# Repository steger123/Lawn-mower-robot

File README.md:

# Lawn-mower-robot

## The main purpose of the project:

**Create a general, affordable, computational platform, which can be used for small & medium size robots.**

The navivation can be: fully maunal, semi and full autonomouse.
The mechanical side not restricted.
As the project progressing and evolving **You can learn more and more**, **and of course, have the designs and codes for free.**

## Software:

### BASE:
Mission Planner: C#
https://github.com/steger123/Lawn-mower-robot/tree/master/03_Software%20codes/02_C%23_Mission%20planner

### ROVER:
Main MCU : C++ (Arduino)
https://github.com/steger123/Lawn-mower-robot/tree/master/03_Software%20codes/01_C%2B%2B_Arduino/01_Rover/Test_Motor_v12

AI: Python (Jetson NANO)
https://github.com/steger123/Lawn-mower-robot/tree/master/03_Software%20codes/03_Python_AI_Jetson%20Nano/01_myOpenCV

### ROVER Electronic boards:
1. Arduino MEGA later Shieldbuddy TC375 (It has 3 cores !)
2. Custom made shield, sitting on the Arduino MEGA to have enough space for connectors (4xseial, 4xSPI, 3xI2C, buttons, 3xultrasonic sensos, volt & ampere meter etc.).
3. GPS: 2 x GNSS modules with RTK / Xbee. More here: https://github.com/steger123/Lawn-mower-robot/issues/8
5. Base's RTK: simpleRTK2Blite from Ardusimple or GPS Development Tools SparkFun GPS-RTK-SMA Breakout - ZED-F9P
6. Rovers RTK: RTK+INS simpleRTK2B-F9R V3 from Ardusimple or SparkFun Accessories SparkFun GPS-RTK Dead Reckoning Breakout - ZED-F9R
7. Motor controllers: 2x DC
8. RF radio: for additional Base to Rover and back communication (remote controll, getting sensor date from rover to mission control software).
9. Jetson Nano with normal webcam. Communicating via serial port to the MEGA (detect plant diseases, following plant line)
10. Sensors on the shield (utlrasonoic distance, battery volt, curret mesuring, rain etc.)

## Body:
As you like. In scouting for example: 1m x 1m x 0.5m

## Wheels:
As you like. In scouting for example: driven 280 mm in diamteter + castor wheels.
it can be smoot like a bicycle or thick lugs like on a tractor tire (good grippong during scouting on the field).

## Engine/motor:
As you like. In scouting for example: 2x 50W DC motors with encoders. 50 rpm

## Transmission:
As you like. In scouting for example: plannetary gerabox.

## Collaboration (software, electronic hardware, new PCB/shield, mechanical parts etc.):
If You like to join, please contact me:
andras.steger@protonmail.com

More information:
https://github.com/steger123/Lawn-mower-robot/wiki

## Latest news:
https://twitter.com/StegerAndras

Custom robot rover shield for Arduino MEGA or ShieldBuddy TC375:

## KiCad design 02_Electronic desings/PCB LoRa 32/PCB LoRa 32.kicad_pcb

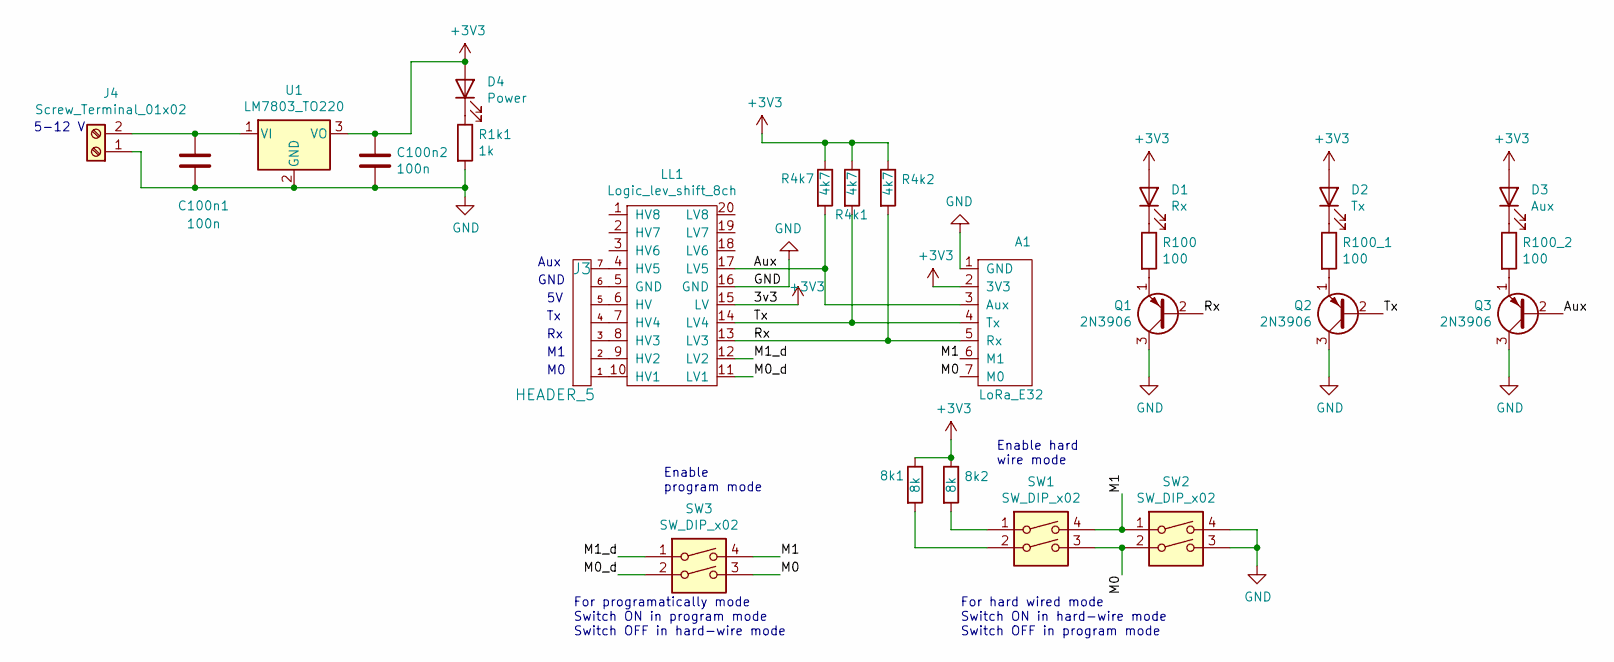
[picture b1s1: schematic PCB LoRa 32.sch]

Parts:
8k1, 8k2: 8k; R_Axial_DIN0204_L3.6mm_D1.6mm_P2.54mm_Vertical
A1: LoRa_E32
C100n1, C100n2: 100n; CP_Radial_Tantal_D5.0mm_P5.00mm
D1: Rx; LED_D5.0mm
D2: Tx; LED_D5.0mm
D3: Aux; LED_D5.0mm
D4: Power; LED_D5.0mm
J3: HEADER_5; JST_XH_B7B-XH-A_1x07_P2.50mm_Vertical
J4: Screw_Terminal_01x02; TerminalBlock_Phoenix_MKDS-1,5-2-5.08_1x02_P5.08mm_Horizont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
LL1: Logic_lev_shift_8ch
Q1, Q2, Q3: 2N3906; TO-92_Inline
R1k1: 1k; R_Axial_DIN0204_L3.6mm_D1.6mm_P2.54mm_Vertical
R4k1, R4k2, R4k7: 4k7; R_Axial_DIN0204_L3.6mm_D1.6mm_P5.08mm_Vertical
R100, R100_1, R100_2: 100; R_Axial_DIN0204_L3.6mm_D1.6mm_P2.54mm_Vertical
SW1, SW2, SW3: SW_DIP_x02; SW_DIP_SPSTx02_Slide_9.78x7.26mm_W7.62mm_P2.54mm
U1: LM7803_TO220; TO-220-3_Vertical

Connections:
+3V3: 8k1.1, 8k2.1, A1.2 (3V3), C100n2.1, D1.2 (A), D2.2 (A), D3.2 (A), D4.2 (A), LL1.15 (LV), R4k1.1, R4k2.1, R4k7.1, U1.3 (VO)
/Aux: A1.3 (Aux), LL1.17 (LV5), Q3.2 (B), R4k7.2
/M0: A1.7 (M0), SW1.3, SW2.2, SW3.3
/M0_d: LL1.11 (LV1), SW3.2
/M1: A1.6 (M1), SW1.4, SW2.1, SW3.4
/M1_d: LL1.12 (LV2), SW3.1
/Rx: A1.5 (Rx), LL1.13 (LV3), Q1.2 (B), R4k2.2
/Tx: A1.4 (Tx), LL1.14 (LV4), Q2.2 (B), R4k1.2
GND: A1.1 (GND), C100n1.2, C100n2.2, J4.1, LL1.16 (GND), Q1.3 (C), Q2.3 (C), Q3.3 (C), R1k1.2, SW2.3, SW2.4, U1.2 (GND)
unnamed: 8k1.2, SW1.2
unnamed: 8k2.2, SW1.1
unnamed: C100n1.1, J4.2, U1.1 (VI)
unnamed: D1.1 (K), R100.1
unnamed: D2.1 (K), R100_1.1
unnamed: D3.1 (K), R100_2.1
unnamed: D4.1 (K), R1k1.1
unnamed: J3.1, LL1.10 (HV1)
unnamed: J3.2, LL1.9 (HV2)
unnamed: J3.3, LL1.8 (HV3)
unnamed: J3.4, LL1.7 (HV4)
unnamed: J3.5, LL1.6 (HV)
unnamed: J3.6, LL1.5 (GND)
unnamed: J3.7, LL1.4 (HV5)
unnamed: Q1.1 (E), R100.2
unnamed: Q2.1 (E), R100_1.2
unnamed: Q3.1 (E), R100_2.2

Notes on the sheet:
5-12 V
For programatically mode Switch ON in program mode Switch OFF in hard-wire mode
For hard wired mode Switch ON in hard-wire mode Switch OFF in program mode
GND
Aux
Enable hard wire mode
Enable program mode

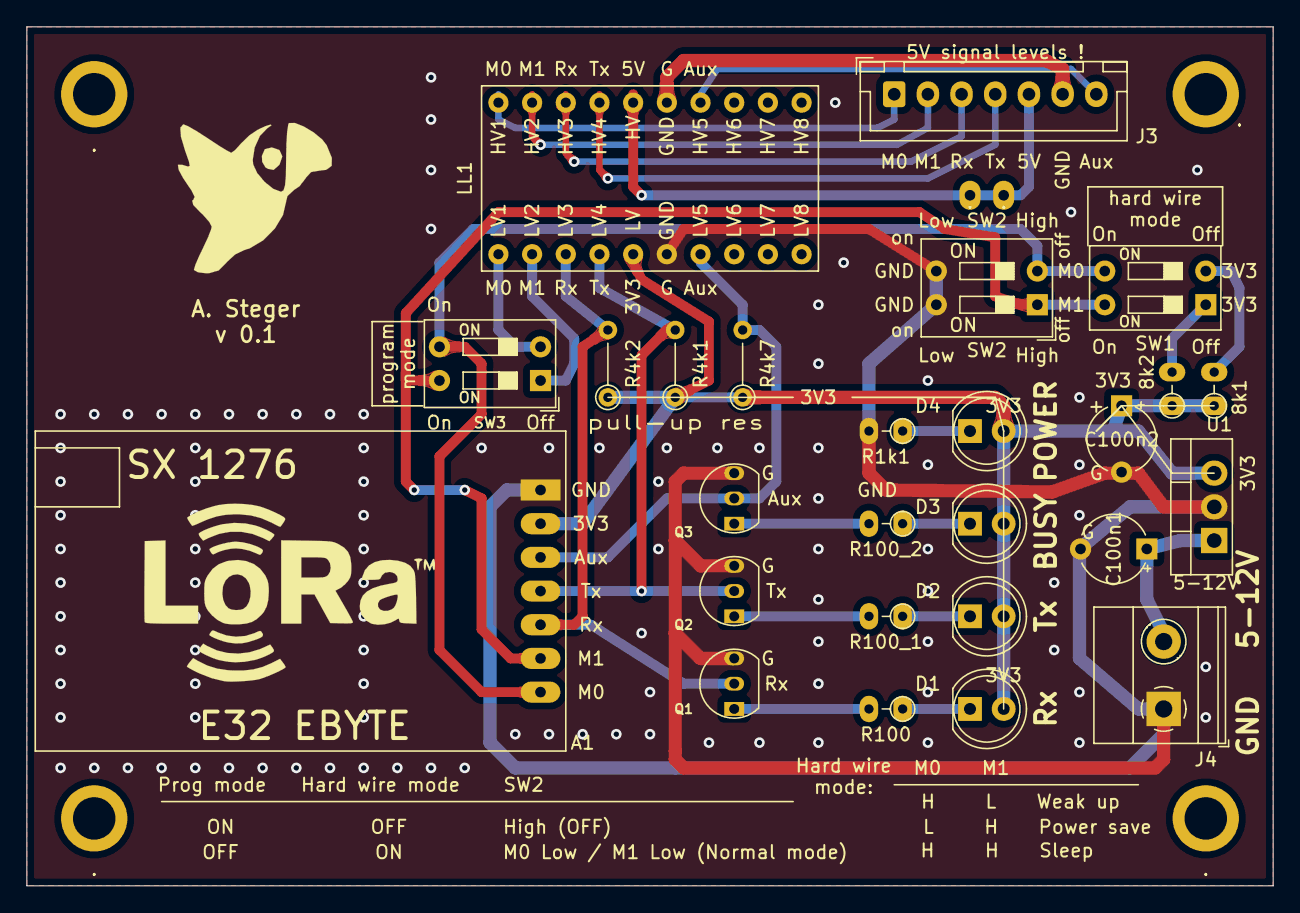
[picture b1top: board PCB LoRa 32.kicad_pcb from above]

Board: 2 copper layers, 94.0 x 64.8 mm, 32 parts (0 on the bottom side), 26 nets.

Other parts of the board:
., .#2: .; 1_pin
.#3, .#4, .#5, .#6: 1pin

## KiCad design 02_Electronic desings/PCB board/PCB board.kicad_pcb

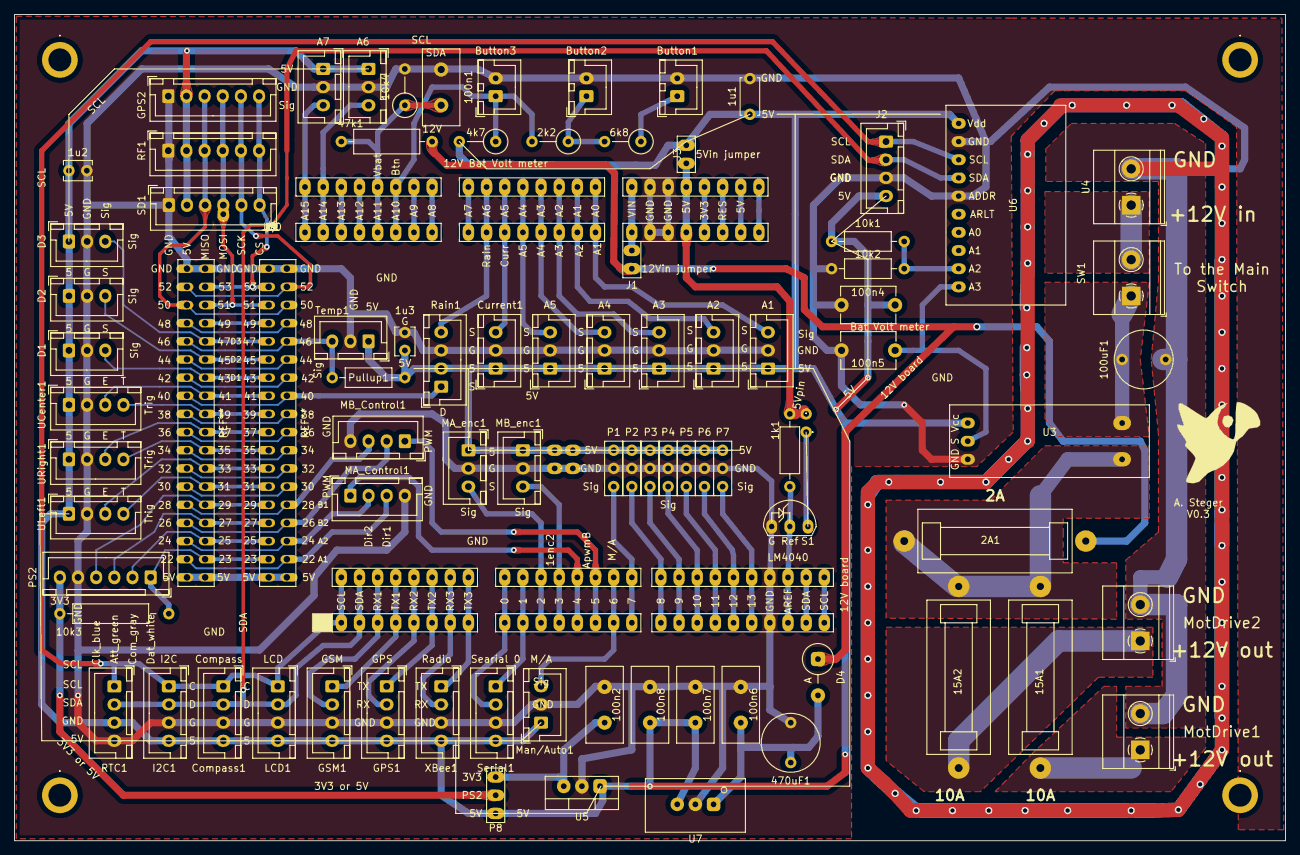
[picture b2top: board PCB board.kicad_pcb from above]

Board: 2 copper layers, 177.8 x 115.6 mm, 105 parts (0 on the bottom side), 68 nets.

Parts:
1k1: 1k; R_Axial_DIN0207_L6.3mm_D2.5mm_P10.16mm_Horizontal
1u1: 1u; C_Disc_D5.0mm_W2.5mm_P5.00mm
1u2, 1u3: 1u; C_Disc_D3.8mm_W2.6mm_P2.50mm
2A1: 2A; Fuse
2k2: 2k2; R_Axial_DIN0309_L9.0mm_D3.2mm_P5.08mm_Vertical
4k7: 4k7; R_Axial_DIN0309_L9.0mm_D3.2mm_P5.08mm_Vertical
6k8: 6k8; R_Axial_DIN0309_L9.0mm_D3.2mm_P5.08mm_Vertical
10k1, 10k2, 10k3: 10k; R_Axial_DIN0207_L6.3mm_D2.5mm_P10.16mm_Horizontal
10k4: 10k; R_Axial_DIN0309_L9.0mm_D3.2mm_P5.08mm_Vertical
15A1, 15A2: 15A1; Fuse
47k1: 47k1; R_Axial_DIN0309_L9.0mm_D3.2mm_P12.70mm_Horizontal
100n1, 100n2, 100n6, 100n7, 100n8: 100nF; C_Disc_D10.5mm_W5.0mm_P5.00mm
100n4, 100n5: 100n; C_Disc_D7.5mm_W5.0mm_P7.50mm
100uF1: 100 uF; C_Radial_D8.0mm_H7.0mm_P3.50mm
470uF1: 470uF; C_Radial_D8.0mm_H7.0mm_P3.50mm
., .#2, .#3, .#4, .#5, .#6, .#7: .; 1_pin
.#8, .#9, .#10, .#11: 1pin
A1, A2, A3, A4, A5, A6, A7: s1; JST_XH_B3B-XH-A_1x03_P2.50mm_Vertical
Button1: TestBtn1; JST_XH_B2B-XH-A_1x02_P2.50mm_Vertical
Button2: TestBtn2; JST_XH_B2B-XH-A_1x02_P2.50mm_Vertical
Button3: TestBtn3; JST_XH_B2B-XH-A_1x02_P2.50mm_Vertical
Compass1: Compass; JST_XH_B4B-XH-A_1x04_P2.50mm_Vertical
Current1: Current sensor; JST_XH_B3B-XH-A_1x03_P2.50mm_Vertical
D1, D2, D3: s1; JST_XH_B3B-XH-A_1x03_P2.50mm_Vertical
D4: 1N4001; D_5W_P5.08mm_Vertical_AnodeUp
GPS1: GPS; JST_XH_B4B-XH-A_1x04_P2.50mm_Vertical
GPS2: GSP rov; JST_XH_B6B-XH-A_1x06_P2.50mm_Vertical
GSM1: GSM; JST_XH_B4B-XH-A_1x04_P2.50mm_Vertical
I2C1: I2C; JST_XH_B4B-XH-A_1x04_P2.50mm_Vertical
J1, J3: HEADER_2; Terminal_p2
J2: ST_01x04; JST_XH_B4B-XH-A_1x04_P2.50mm_Vertical
J5, J6, J7, J9, J10, J11, J15, J16, J18, J19: .; Terminal_p8
J14, J17: .; Terminal_p10
LCD1: LCD display; JST_XH_B4B-XH-A_1x04_P2.50mm_Vertical
MA_Control1: MA_Control; JST_XH_B4B-XH-A_1x04_P2.50mm_Vertical
MA_enc1: MA_enc1; JST_XH_B3B-XH-A_1x03_P2.50mm_Vertical
MB_Control1: MB_Control; JST_XH_B4B-XH-A_1x04_P2.50mm_Vertical
MB_enc1: MB encoder; JST_XH_B3B-XH-A_1x03_P2.50mm_Vertical
Man/Auto1: Switch Manual/Auto; JST_XH_B3B-XH-A_1x03_P2.50mm_Vertical
MotDrive1: 12V Mot1 OUT; TerminalBlock_Phoenix_MKDS-1,5-2-5.08_1x02_P5.08mm_Horizont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
MotDrive2: 12V Mot2 OUT; TerminalBlock_Phoenix_MKDS-1,5-2-5.08_1x02_P5.08mm_Horizont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
P1, P2, P3, P4, P5, P6, P7: HEADER_3; Terminal_p3_sp
P8: HEADER_3; Terminal_p3
PS2: PS2_Controll; JST_XH_B6B-XH-A_1x06_P2.50mm_Vertical
Pullup1: 4k7; R_Axial_DIN0207_L6.3mm_D2.5mm_P10.16mm_Horizontal
RF1: RF rov; JST_XH_B6B-XH-A_1x06_P2.50mm_Vertical
RTC1: RTC; JST_XH_B4B-XH-A_1x04_P2.50mm_Vertical
Rain1: Rain Sensor; JST_XH_B4B-XH-A_1x04_P2.50mm_Vertical
S1: LM4040 2.5V; TO-92
SD1: SD card; JST_XH_B6B-XH-A_1x06_P2.50mm_Vertical
SW1: SW_DIP_x01; TerminalBlock_Phoenix_MKDS-1,5-2-5.08_1x02_P5.08mm_Horizont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
Serial1: Serial 0; JST_XH_B4B-XH-A_1x04_P2.50mm_Vertical
Temp1: Temp sensor; JST_XH_B3B-XH-A_1x03_P2.50mm_Vertical
U3: ACS712_30A; ASC712
U4: ST; TerminalBlock_Phoenix_MKDS-1,5-2-5.08_1x02_P5.08mm_Horizont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
U5: LM7803_TO220; TO-220-3_Vertical
U6: ADS1115
U7: LM7805_TO220; Traco_TSR2
UCenter1: Ultrason_Right; JST_XH_B4B-XH-A_1x04_P2.50mm_Vertical
ULeft1: Ultrasonic Left; JST_XH_B4B-XH-A_1x04_P2.50mm_Vertical
URight1: Ultrason_Right; JST_XH_B4B-XH-A_1x04_P2.50mm_Vertical
XBee1: XBee; JST_XH_B4B-XH-A_1x04_P2.50mm_Vertical

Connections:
+3V3: 100n2.1, P8.3, U5.3
+5P: 1u1.1, 1u2.1, 1u3.1, 4k7.2, 10k1.1, 100n4.1, 100n7.1, 100n8.1, .#4.1, .#5.1, A1.1, A2.1, A3.1, A4.1, A5.1, A6.1, A7.1, Compass1.4, Current1.1, D1.1, D2.1, D3.1, GPS1.4, GPS2.2, GSM1.4, I2C1.4, J2.4, J3.2, LCD1.4, MA_enc1.1, MB_enc1.1, Man/Auto1.1, P1.3, P2.3, P3.3, P4.3, P5.3, P6.3, P7.3, P8.1, Pullup1.1, RF1.2, RTC1.3, Rain1.2, SD1.2, Serial1.4, Temp1.1, U3.4, U5.1, U6.1, U7.3, UCenter1.1, ULeft1.1, URight1.1, XBee1.4
+12V: 2A1.1, 47k1.1, D4.1, J1.2
/5Vpin: 1k1.1, J3.1, J5.5, J9.5
/A1: A1.3, J6.1, J10.1
/A2: A2.3, J6.2, J10.2
/A3: A3.3, J6.3, J10.3
/A4: A4.3, J6.4, J10.4
/A5: A5.3, J6.5, J10.5
/A6: A6.3, J7.7, J11.7
/A7: A7.3, J7.8, J11.8
/AREF: 1k1.2, J14.8, J17.8, S1.1
/Button: 2k2.2, 4k7.1, Button3.1, J7.3, J11.3
/CS: GPS2.6, RF1.6, SD1.6
/CurA: 100uF1.1, SW1.1, U3.1
/CurB: 2A1.2, 15A1.1, 15A2.1, U3.2
/Current: Current1.3, J6.6, J10.6
/M1Enc: J15.3, J18.3, MA_enc1.3
/M2Enc: J15.4, J18.4, MB_enc1.3
/MISO: GPS2.3, RF1.3, SD1.3
/MOSI: GPS2.4, RF1.4, SD1.4
/ManualMode: J15.7, J18.7, Man/Auto1.3
/PS2_Data: 10k3.2, PS2.1
/PWM_1: J15.8, J18.8, P1.1
/PWM_2: J14.1, J17.1, P2.1
/PWM_3: J14.2, J17.2, P3.1
/PWM_4: J14.3, J17.3, P4.1
/PWM_5: J14.4, J17.4, P5.1
/PWM_6: J14.5, J17.5, P6.1
/PWM_7: J14.6, J17.6, P7.1
/PWM_A: J15.5, J18.5, MA_Control1.1
/PWM_B: J15.6, J18.6, MB_Control1.1
/RX0: J15.1, J18.1, Serial1.2
/RX1: GSM1.2, J16.3, J19.3
/RX2: GPS1.2, J16.5, J19.5
/RX3: J16.7, J19.7, XBee1.2
/RainA: J6.7, J10.7, Rain1.4
/SCK: GPS2.5, RF1.5, SD1.5
/SCL: Compass1.1, I2C1.1, J2.1, J16.1, J19.1, LCD1.1, RTC1.1, U6.3
/SDA: Compass1.2, I2C1.2, J2.2, J16.2, J19.2, LCD1.2, RTC1.2, U6.4
/TX0: J15.2, J18.2, Serial1.1
/TX1: GSM1.1, J16.4, J19.4
/TX2: GPS1.1, J16.6, J19.6
/TX3: J16.8, J19.8, XBee1.1
/Temp: Pullup1.2, Temp1.3
/VBat: 10k4.1, 47k1.2, 100n1.1, J7.4, J11.4
/VINpin: J1.1, J5.8, J9.8
GND: 1u1.2, 1u2.2, 1u3.2, 10k2.2, 10k4.2, 100n1.2, 100n2.2, 100n4.2, 100n5.2, 100n6.2, 100n7.2, 100n8.2, 100uF1.2, 470uF1.2, A1.2, A2.2, A3.2, A4.2, A5.2, A6.2, A7.2, Button1.2, Button2.2, Button3.2, Compass1.3, Current1.2, D1.2, D2.2, D3.2, GPS1.3, GPS2.1, GSM1.3, I2C1.3, J2.3, J5.6, J5.7, J9.6, J9.7, J14.7, J17.7, LCD1.3, MA_Control1.4, MA_enc1.2, MB_Control1.4, MB_enc1.2, Man/Auto1.2, MotDrive1.2, MotDrive2.2, P1.2, P2.2, P3.2, P4.2, P5.2, P6.2, P7.2, PS2.5, RF1.1, RTC1.4, Rain1.3, S1.2, SD1.1, Serial1.3, Temp1.2, U3.5, U4.2, U5.2, U6.2, U6.5, U7.2, UCenter1.2, ULeft1.2, URight1.2, XBee1.3
unnamed: 2k2.1, 6k8.2, Button2.1
unnamed: 6k8.1, Button1.1
unnamed: 10k1.2, 10k2.1, U6.9
unnamed: 10k3.1, P8.2, PS2.6
unnamed: 15A1.2, MotDrive1.1
unnamed: 15A2.2, MotDrive2.1
unnamed: 100n5.1, U3.3, U6.10
unnamed: 100n6.1, 470uF1.1, D4.2, U7.1
unnamed: J5.1, J9.1
unnamed: J5.2, J9.2
unnamed: J5.3, J9.3
unnamed: J5.4, J9.4
unnamed: J6.8, J10.8
unnamed: J7.1, J11.1
unnamed: J7.2, J11.2
unnamed: J7.5, J11.5
unnamed: J7.6, J11.6
unnamed: J14.9, J17.9
unnamed: J14.10, J17.10
unnamed: SW1.2, U4.1

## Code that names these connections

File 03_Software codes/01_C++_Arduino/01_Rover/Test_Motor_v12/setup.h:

//*********** Global Variables: ***********
float VBat;                  // Battery voltage [V]
float VBatPC;                // Battery voltage percentage
#define VBat_Level_Min  10.0
#define VBat_Level_Max  13.8
#define IBat_Max 2.0         // defines the maximum permissible current to the full device ACS712

const unsigned long BatVoltMax = 13500; //mV
const unsigned long BatVoltMin = 10400; //mV
const unsigned long BatRs[]    = {47250, 10020};    // 47150 or 45300 or 45390 or 45900 ; 47k & 10k = R2 & R3 in ohm, must be measured accurately before soldering !!!
double InverseVoltDividerRatio = 5.6918; //divison give only integer !; //5.7355289421157684630738522954092
const unsigned int NrSamples   = 10;    // Usually from 5 to 64 How many samples to be taken for batVolt measuring

float batTemp;             // Battery temperature
int compassHeading;
boolean rain;
//float ISupply;  //Instead of ICut , but IPanel (for solar panel requried)
long ISupply;

#define timeReverse 3000  // duration reverse motor when obstacle detect
#define timeRotate  2000  // duration rotate motor when obstacle detect
#define USdistance  100   // obstacle distance for ultrasonic sensor
int USDistaneLeft;        // Utrasonic sensor distance in cm
int USDistaneRight;
int USDistaneCenter;

unsigned long previousMillis = 0;
unsigned long currentMillis; 
#define timeClock   500   // time diffrence for reading new sensor data
volatile int mowerStatus=0; // 0=oncharge (press pen for run)
                            // 1=run
                            // 2=stuck
                            // 3=search
                            // 4=batlow
                            // 5=charge and restart when full
                            // 6=raining
                            // 7=current too much on the battery/motor controller
volatile unsigned long wheelTime = 0;
                            
#define accelerateTime   50   // 2 total time accelerate [msec]
int encCountA = 0;          // how many times the encoders wheel tunred 
int wheelTurnCount = 0;              // one wheel tunr = 1240 turn on encoder's wheel. How many wheel turn required for X meter.
String mode = "---";      // this required in Interrrup, becuse for turn (aling heading to bearing) less ecoder tick reuires than cover distance.
int turnTickCount = 0;      //how many ecoder tick required lat se for X degree tunr

int PWM_speed   = 0;          // actual speed of the robot, first select "start" to start the robot
int oldSpeed    = 0;          // for proper acceleration 
int wheelTurnRequired    = 0;
String robDirection = "st";   // start
String prevDirection;
int gear        = 2;
boolean startMotor = false;
int i;                        // for 'for' cyclus
int error =     0;
byte type =     0;
byte vibrate =  0;

int BtnMotor  = 1;
int BtnSensor = 2;
int BtnOther  = 3;

// ***** Digital pins: ******
#define manualMode_pin    6
#define remoteMode_pin    7


#define Encoder_pin_A    2   // 2 INT4 Signal pin # Encoder_A- from encoder UNO only: 2 & 3 pins ! MEGA only: 2, 3, 18, 19, 20, 21
#define Encoder_pin_B     3    // 3 INT5 Signal pin # Encoder_B - from encoder
//#define Panel_pin         8  // Solar panel on/off

#define PWMA_pin          4    // 4 PWM; orange PWM_A                   enable_A
#define motDIR_pin_A1    22    // 6 IN-1 ; Direction_1; brown  DIR_A1  motor_A1
#define motDIR_pin_A2    24    // 5 IN-2 ; Direction_2; green  DIR_A2  motor_A2 
#define PWMB_pin          5    // 8 PWM; orange PWM_pin_B                   enable_B 
#define motDIR_pin_B1    28    // 9 IN-2 ; Direction_1; green  DIR_B1  motor_B1 
#define motDIR_pin_B2    26    // 10 IN-1 ; Direction_2; brown DIR_B2  motor_B2

#define Trig_pinL  31  //Ultrasonic LEFT
#define Echo_pinL  33
#define Trig_pinR  35  //Ultrasonic RIGHT
#define Echo_pinR  37
#define Trig_pinC  39  //Ultrasonic CENTER
#define Echo_pinC  41

#define Temp_pin 46   // for temperature sensor

//**** Analog pins: ******
#define Button_pin     A10  // #A10 Push button pin
#define BatVolt_Pin    A11  // #A11 Battery voltage const byte BatVoltPin = A11;     //Analog pin # A11
#define IBat_pin       A5  // Battery supply full current with ACS712
#define RainingA_pin   A6  // Rain drop sensor anlaoge output
#define RainingD_pin   40  // Rain drop sensor digital output 

#define SDA_pin        20  // #20 SDA for I2C
#define SCL_pin        21  // #21 SCL for I2C

//#define BatVolt_Pin 2  // ???? A11

void setupPins(){
  pinMode(motDIR_pin_A1,  OUTPUT);
  pinMode(motDIR_pin_A2,  OUTPUT);
  pinMode(PWMA_pin,       OUTPUT);
  pinMode(motDIR_pin_B1,  OUTPUT);
  pinMode(motDIR_pin_B2,  OUTPUT);
  pinMode(PWMB_pin,       OUTPUT);
  //  pinMode(A_Signal_Enc, INPUT);
  pinMode(Encoder_pin_A,  INPUT_PULLUP);
  //pinMode(Encoder_pin_A,  INPUT);
   pinMode(Encoder_pin_B,  INPUT_PULLUP);
  //pinMode(Encoder_pin_B,  INPUT);
  pinMode(manualMode_pin, INPUT);
  //  pinMode(Panel_pin,      OUTPUT);  //solar panel
  pinMode(manualMode_pin, INPUT);

  digitalWrite(motDIR_pin_A1, LOW);
  digitalWrite(motDIR_pin_A2, LOW);
  digitalWrite(motDIR_pin_B1, LOW);
  digitalWrite(motDIR_pin_B2, LOW);
  analogWrite(PWMA_pin, 0);
  analogWrite(PWMB_pin, 0);
  //  digitalWrite(Panel_pin, LOW);

  // Sensors ?:
  //pinMode(Button_pin, INPUT);
  //analogWrite(Button_pin, HIGH);
  pinMode(Trig_pinL, OUTPUT);
  pinMode(Echo_pinL, INPUT);
  pinMode(Trig_pinR, OUTPUT);
  pinMode(Echo_pinR, INPUT);
  pinMode(Trig_pinC, OUTPUT);
  pinMode(Echo_pinC, INPUT);
}

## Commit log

2020-06-24 Rename pyyhonToODrive.py to pythonToODrive.py
2020-06-24 Create servoPS4control
2020-06-24 Files for better sevo controll understanding
    Source: https://www.youtube.com/watch?v=RnGUTny1hG8
2020-06-24 Proposal detail for one concpt
2020-06-24 Guidence for Conceptual design
    The different variants halping to find the right solution and optimise the desing.
2020-06-24 Updated list
2020-06-24 Text changed
2020-06-25 Concept designs
2020-06-25 Desing change
2020-06-25 Design status
2020-06-25 e-mail adress added
2020-06-25 Wiki added
2020-06-26 Desing upgrade
2020-06-26 New e-mail address
2020-06-26 Install Adafruit PCA9685 Python library
2020-06-26 Servo code and connection
2020-06-29 New codes added
2020-06-30 Routing update
2020-06-30 Routing issue solved.
2020-07-02 Rover JS update
2020-07-04 Enhancement main file
2020-07-04 New modules
2020-07-04 Lawn mower robot logo
2020-07-04 Read Me!
2020-07-04 Removed
2020-07-04 Deleted
2020-07-07 Update delete marker & line
2020-07-21 New updates
2020-11-02 Shield for Arduino MEGA
    PCB shield for Arduino MEGA (with Jetson Nano, UNO, XBee, radio contoller , 2xmotor contollers, 2xencoders etc. connetions).
2020-11-02 Shield for Arduino MEGA
    Can be connected: Jetson Nano, radio contoller, 2xUART, 2xmotor contollers, 2xencoders with less wiring.
2020-11-02 PCB board pictures
    Working :-) no smoke !
2021-05-04 Update
    New version
2021-05-04 Dataset for weeds
    https://github.com/steger123/DeepWeeds
2021-05-04 Upade
    new version
2021-05-04 Update
    New version.
2021-05-04 Disease detection
2021-05-04 Image recognition
    Codes for Jetson Nano
2021-05-05 Update
    Latest pictures
2021-05-05 Resized
    It was too big
2021-05-05 Resized
2021-05-05 Logo
2021-05-05 How to start ?
2021-05-05 How to start ?
    The first steps.
2021-05-05 How to start ?
    Integrate in VS the GMap.NET Nuget package.
2021-05-07 Shield pdf drawings added
    Explanation how to use for ESC motor as well.
2021-05-08 Update on ultrasonic sensor
2021-05-13 Create Robot Rover PCB Manual_v0.2.0.pptx
    PCB manual added
2021-06-18 LoRa breakout board
    LoRa breakout board
2021-06-18 LoRa 862MHz + CHAN * 1MHz
    How program to : 862MHz + CHAN * 1MHz
2021-06-18 Get settings for 868 MHz LoRa SX 1276 RF long range E32-868T30D module
    Get settings for 868 MHz LoRa SX 1276 RF long range E32-868T30D module
2021-08-26 Created using Colaboratory
